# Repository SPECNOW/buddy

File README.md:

buddy
=====

# SPEC Robot
Clark Was able to clone this repository located at 
git@github.com:SPECNOW/buddy.git

## ADC Module
* Uses ADC and nHET modules
* Using 6 channels on ADC with nHET1_8 as the Triggger
* nHET PWM set for nHET1_8 @ 50% Duty Cycle @ 1 kHz
* Last 10 samples are reported by print ADC info

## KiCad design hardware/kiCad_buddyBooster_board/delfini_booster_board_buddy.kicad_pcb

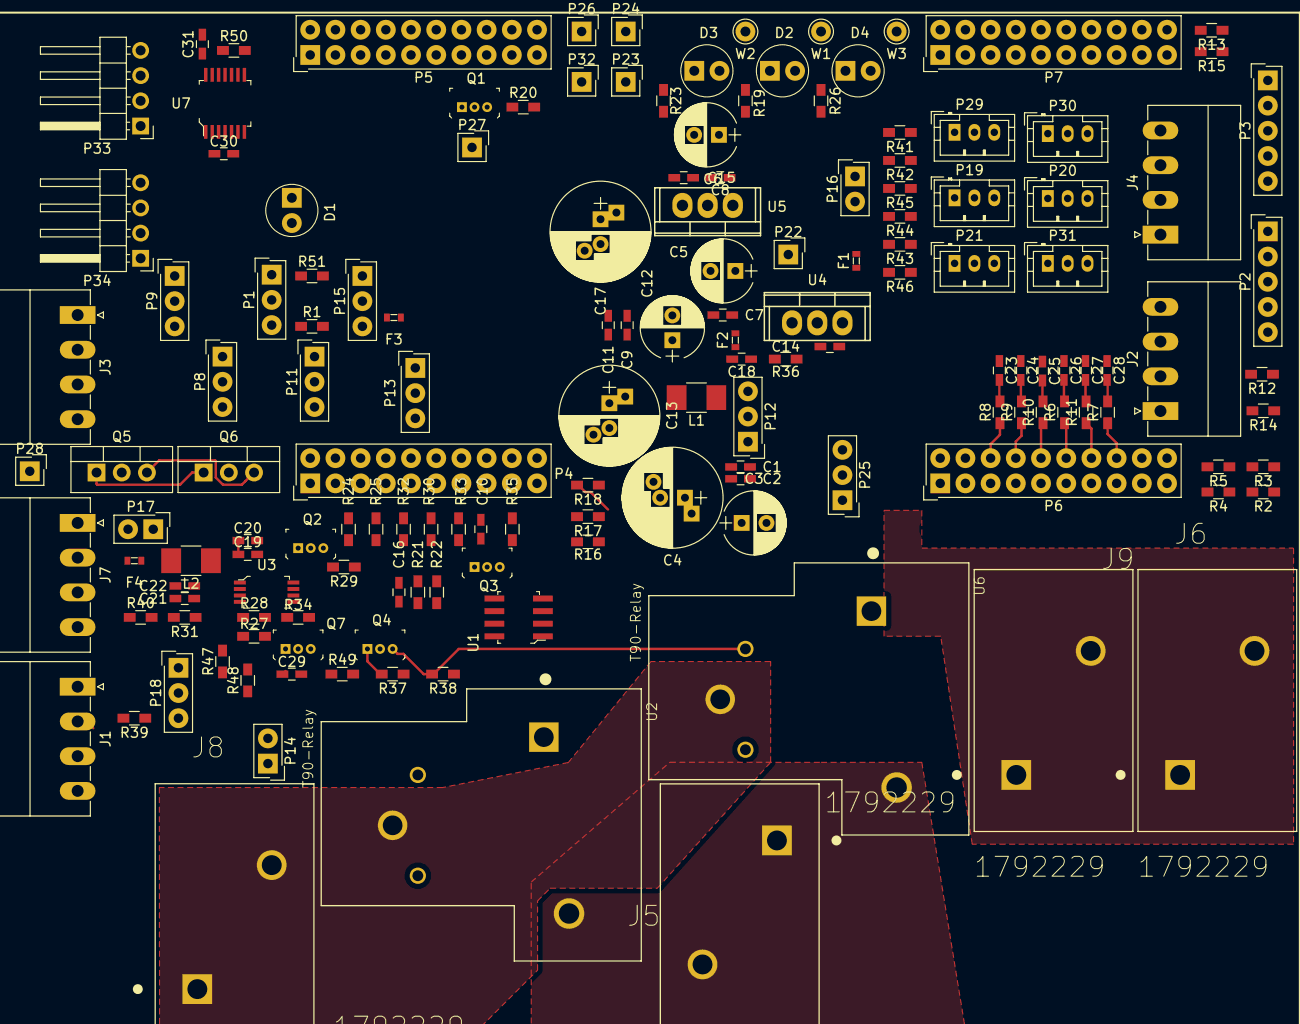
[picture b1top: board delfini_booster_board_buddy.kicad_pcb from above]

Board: 2 copper layers, 151 parts (0 on the bottom side), 88 nets.

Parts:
C1, C2, C7, C8, C9, C10, C11, C14, C15, C16, C19, C21, C23, C24, C25, C26, C27, C28, C29: C_Small; C_0603_HandSoldering
C3, C12: CP_Small; CP_Radial_D6.3mm_P2.50mm
C4, C13: CP_Small; CP_Radial_D10.0mm_P2.50mm_P5.00mm
C5, C6: CP1_Small; CP_Radial_D6.3mm_P2.50mm
C17: CP1_Small; CP_Radial_D10.0mm_P2.50mm_P5.00mm
C18, C20, C22: CP_Small; C_0603_HandSoldering
C30, C31: 0.1u; C_0603_HandSoldering
D1, D2, D3, D4: LED; LED_3mm_Radial
F1, F2, F3, F4: Fuse_Small; 0603
J1, J2, J3, J4, J7: Screw_Terminal_1x04; PhoenixContact_MC-G_04x3.50mm_Angled
J5, J6, J8, J9: 1792229; PHOENIX_1792229
L1, L2: Ferrite_Bead_Small; R_1210_HandSoldering
P1, P8, P9, P11, P12, P13, P15, P18, P25: CONN_01X03; SL-103-X-XX_1x03
P2, P3: CONN_01X05; SL-105-X-XX_1x05
P4, P5, P6, P7: CONN_02X10; SDL-120-X-XX_2x10
P14, P16, P17: CONN_01X02; SL-102-X-XX_1x02
P19, P20, P21, P29, P30, P31: CONN_01X03; JST_PH_B3B-PH-K_03x2.00mm_Straight
P22, P23, P24, P26, P27, P28, P32: CONN_01X01; SL-101-X-XX_1x01
P33, P34: CONN_01X04; Pin_Header_Angled_1x04_Pitch2.54mm
Q1, Q2, Q3, Q4, Q7: 2N7002; TO-92-3
Q5, Q6: IRF9540N; TO-220-3_Vertical
R1, R2, R3, R4, R5, R6, R7, R8, R9, R10, R11, R12, R13, R14, R15, R16, R17, R18, R19, R20, R21, R22, R23, R24, R25, R26, R27, R28, R29, R30, R31, R32, R33, R34, R35, R36, R37, R38, R39, R40, R41, R42, R43, R44, R45, R46, R47, R48, R49, R50, R51: R; R_0603_HandSoldering
U1: TMP275; SOIC-8_W3.9mm
U2, U6: T90-Relay; RELAY_1-1393209-2
U3: tps2112a; TSSOP-8_W4.4mm
U4: LM7812; TO-220
U5: R-783.3-1.0; TO-220
U7: TXB0104; TSSOP-14_W4.4mm
W1, W2, W3: TEST_1P; Pin_d1.0mm_L10.0mm

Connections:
+3V3: C16.2, C30.1, D3.2, F3.1, P26.1, R1.2, R2.1, R3.1, R16.1, R17.1, R18.1, R20.2, R21.1, R25.2, R31.2, R32.2, R35.2, R40.2, R47.2, R51.2, U1.8, U7.1, W2.1
+5V: C31.1, D2.2, P13.1, P17.1, P19.1, P20.1, P21.1, P24.1, P29.1, P30.1, P31.1, P33.1, P34.1, R12.2, R13.2, R14.2, R15.2, R50.1, U2.1, U7.14, W1.1
+12V: D4.2, J2.4, J4.4, P16.1, P23.1, W3.1
/5V_DEV_BRD: P8.2, R28.1, U3.6
/ADC0_IN_C2000: C23.2, R8.2, R41.2
/ADC0_OUTPUT: P29.2, R41.1
/ADC1_IN_C2000: C24.2, R9.2, R42.2
/ADC1_OUTPUT: P30.2, R42.1
/ADC2_IN_C2000: C25.2, R10.2, R43.2
/ADC2_OUTPUT: P31.2, R43.1
/ADC3_IN_C2000: C26.2, R6.2, R44.2
/ADC3_OUTPUT: P19.2, R44.1
/ADC4_IN_C2000: C27.2, R11.2, R45.2
/ADC4_OUTPUT: P20.2, R45.1
/ADC5_IN_C2000: C28.2, R7.2, R46.2
/ADC5_OUTPUT: P21.2, R46.1
/BAT_PWR_IN: C1.1, C2.1, C3.1, C4.1, J5.1, J5.2, P12.1, Q5.3, Q6.3, R49.2, U2.5, U6.5
/BAT_PWR_OUT: J8.1, J8.2, U2.3, U6.3
/BAT_PWR_OUT_DELFINO_EN: P5.1, R24.1
/BAT_PWR_OUT_EN: P11.1, Q2.1, Q4.1, R24.2, R25.1, R29.2, R37.2
/BRD_ID0: P6.17, R2.2, R4.1
/BRD_ID1: P6.19, R3.2, R5.1
/E_BRAKE_EN: P9.1, Q1.1, Q3.3, R35.1
/E_BRAKE_IN: J1.2, P18.3, R30.2
/LAUNCHPAD_5V: P4.2, P6.2, P8.1
/LaunchPad_3V3: P4.1, P6.1, P15.3
/MOTOR_BRAKE_EN: P9.2, R47.1, R48.2
/MOTOR_BRAKE_EN_N: Q5.1, Q6.1, Q7.3, R49.1
/RELAY_COIL: Q2.3, R38.1, U2.2
/SABERTOOTH_5V: J7.3, R27.2, U3.8
/SCL_4.7K: P4.19, R17.2, U1.2
/SDA_4.7K: P4.17, R16.2, U1.1
/TEST_EN_N: P1.3, P4.5, R1.1
/TMP275_ALERT_OD: P4.15, R18.2, U1.3
/TO_ENCODER_L_A: J2.3, P2.1
/TO_ENCODER_L_B: J2.2, P2.2
/TO_ENCODER_R_A: J4.3, P3.1
/TO_ENCODER_R_B: J4.2, P3.2
/TPS_STAT: R31.1, U3.1
/UART_SABER_TX: J7.1, P6.13
/ULTRA0_PULSE_BACK: P33.3, U7.12
/ULTRA0_PULSE_BACK_BUFFD: P5.9, U7.3
/ULTRA0_TRIG_OUT: P33.2, U7.13
/ULTRA0_TRIG_OUT_BUFFD: P5.5, U7.2
/ULTRA1_PULSE_BACK: P34.3, U7.10
/ULTRA1_PULSE_BACK_BUFFD: P5.11, U7.5
/ULTRA1_TRIG_OUT: P34.2, U7.11
/ULTRA1_TRIG_OUT_BUFFD: P5.7, U7.4
GND: C1.2, C2.2, C3.2, C4.2, C5.2, C6.2, C7.2, C8.2, C9.2, C10.1, C11.2, C12.2, C13.2, C14.2, C15.2, C16.1, C17.2, C19.2, C20.2, C21.2, C22.2, C23.1, C24.1, C25.1, C26.1, C27.1, C28.1, C29.2, C30.2, C31.2, D1.1, J2.1, J3.2, J3.4, J4.1, J7.4, P1.2, P2.5, P3.5, P4.4, P5.2, P6.4, P7.2, P14.2, P19.3, P20.3, P21.3, P25.2, P27.1, P28.1, P29.3, P30.3, P31.3, P32.1, P33.4, P34.4, Q1.2, Q2.2, Q3.2, Q4.2, Q7.2, R4.2, R5.2, R19.2, R22.1, R23.2, R26.2, R29.1, R33.1, R34.2, R36.1, R37.1, R39.2, U1.4, U1.5, U1.6, U3.5, U4.2, U5.2, U7.7
unnamed: C10.2, Q3.1, R30.1, R32.1, R33.2
unnamed: C9.1, C11.1, C12.1, C13.1, C18.1, F2.1, L1.2
unnamed: C14.1, F1.1, U4.3
unnamed: C15.1, C17.1, P15.1, U5.3
unnamed: C18.2, R36.2
unnamed: C19.1, C20.1, L2.1, U3.7
unnamed: C21.1, C22.1, F4.1, L2.2
unnamed: C29.1, Q7.1, R48.1
unnamed: D1.2, P1.1, R51.1
unnamed: D2.1, R19.1
unnamed: D3.1, R23.1
unnamed: D4.1, R26.1
unnamed: F1.2, P16.2
unnamed: F3.2, P15.2
unnamed: F4.2, P17.2
unnamed: J1.1, P18.2, R39.1, R40.1
unnamed: J3.1, Q6.2
unnamed: J3.3, Q5.2
unnamed: J6.1, J6.2, J9.1, J9.2, P25.1
unnamed: L1.1, P12.2
unnamed: P2.3, R12.1
unnamed: P2.4, R14.1
unnamed: P3.3, R13.1
unnamed: P3.4, R15.1
unnamed: P6.6, R8.1
unnamed: P6.8, R9.1
unnamed: P6.10, R10.1
unnamed: P6.12, R6.1
unnamed: P6.14, R11.1
unnamed: P6.16, R7.1
unnamed: P11.2, Q1.3, R20.1
unnamed: P13.2, U6.1
unnamed: P14.1, U3.2
unnamed: Q4.3, R38.2, U6.2
unnamed: R21.2, R22.2, U1.7
unnamed: R27.1, R28.2, U3.3
unnamed: R34.1, U3.4
unnamed: R50.2, U7.8
VAA: C5.1, C6.1, C7.1, C8.1, F2.2, P22.1, U4.1, U5.1

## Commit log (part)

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2013-12-13 create folder structure
2013-12-13 Clark modified README.md for his first git clone and git add, git commit and git push eventually. try using git commit -m "here is your one liner comment"
2014-05-30 tracking the green plate successful.
2014-06-06 swich from searching the whole image to scanning the submat but it crashes when it moves off screen
2014-06-09 Added Additional changes
2014-06-20 Changed the Image Data from a Depth Cloud to a Point Cloud for the Depth Converter. Added PointCloud Dependencies to project.
2014-06-26 Update DepthConverter.cpp
    We forgot to multiply the column index by 4.
2014-07-31 Ian finally does git. Also, this is a test
2014-08-04 Ian prepares for work on github
    ARM stuff works so testing the wireless MSP430 and writing dead reckoning code is coming
2014-09-11 Added Sensor Classes for IR and Sonar
    + Added GP2Y0A21YK (Sharp IR) Sensor Library
    + Created wrapper class for IR Sensor based off of common base Sensor
    Class
    + Added Sonar Sensor class based off of common base Sensor Class
2014-09-11 Motor turn with hardware serial1 on tx1
    We use the void setup to set up. use void loop for the main code.
    currently we have it sending 65 which is stop.
2014-09-11 interupt code change
    changed the interupt pin. it was 2 and 3, but instead use 0 and 1, as
    it is INTERUPT 0 and INTERUPT 1, not ... PIN3 PIN2.
    Have not tested with our set up. but i did simple test to turn some led
    on off and found the error
2014-09-11 Interrupts works- cleaned up testing code
    - Cleaned up some testing print outs
    - rearranged some function calls
2014-09-11 Revert "Update sketch_aug21a.ino"
    This reverts commit 9fc85e1593c4273154ef5ad6b182527779132d55.
2014-09-11 back update
    merged some changed.
2014-09-11 testing with encoder (fake)
    testing the QEM and the dir of encoder
2014-09-15 Fixed Sensor Class
    * Fixed Sonar and IR and verified that they are working correctly
    + Added Example Arduino Code for Sensor classes
2014-09-18 accident. ill revert
2014-09-18 Revert "accident. ill revert"
    This reverts commit 0923a94fb17245c32524b4a91cd5953422873def.
2014-10-02 Serial Test for MSP430G2553
    Tried Getting UART to work for MSP430, works by criss-crossing the RX
    and TX jumpers for Emultor board
2014-10-09 + Intial attemp at getting Buddy's Motor Controller to work on MSP430 MCU instead of Arduino. + Created Serial and MotorStateMachine Structs
2014-10-13 Fixed up previous code
    Code compiles correctly now, but doesn't work correctly. Further
    investigation needed.
2014-12-04 + Initial Commit of Hercules Buddy Motor Encoder Code
2015-09-10 Past 8 Months of work
    + ADC "working"
    + HET/Ultrasonic "working". Added Sonar Sensor Data Structures.
    + DAC working
    + Added Debugging/Info Message wrapper function (print_info, etc.)
    + Added Defines files for global variables
    + Fixed up Muxes/Interrupts/etc. in HalCoGen
2015-10-01 Moved our main project folder from Buddy_MotorEncoder_R4 to Buddy_Firmware_Hercules
2015-10-08 * Fixed Issue with BuddyFirmware_HalCoGen.hcg not working correctly (from previous commit) + Added rtiCounter for doing sonar PWM instead of HET (HET will still do the capture return from the sonar s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
2015-10-15 added ir_adc.h and .c created prototypes
2015-10-21 Sonar Sort of Works
    * nHET Capture returns Ultrasonic Pulse width correctly and calculates
    the distance correctly, but the Timeout implementation does not work
2016-01-21 Changed the method to do the Sonar Echo Capture to use RTI clock
    * Changed Sonar Echo Capture method to sample the RTI clock at the
    rising and falling edge of the Echo Signal and do math to figure out the
    signal width in milliseconds and then convert it to centimeters
    * RTI Trigger seems to have a problem with sonar 2, sonar 1 works fine
    both by itself and with sonar 2 enabled. May be due to interrupts for
    triggers for sonar 1 and sonar 2 happening at the same time?
2016-02-04 Added some comments for the Sonar/UltraSonic Stuff
    + Added some comments for the Sonar/UltraSonic Stuff
2016-03-31 Updated GitIgnore to Ignore C\C++, Python, Eclipse General Ignorable files
2016-03-31 removed laptop-software/motor-control-drivers/senor-to-laser/sensor-to-laser-base.py~
2016-04-07 -renamed senor-to-laser to sensor-to-laser
2016-04-14 Renamed the file so it would have _ instead of - in the name
2016-05-05 - created workspace in buddy/laptop-software - ros packages are in buddy/laptop-software/src/
2016-05-05 -moved some files into src
2016-05-05 Moving Serial Node to appropriate Folder
2016-06-02 * Updated Serial Node so that data is correctly extracted from serial data messages
2016-06-02 -added msg folder, didnt know it didnt work
2016-06-16 Made changes to CMake for Python
2016-07-14 Moved serial_node.py to scripts/ and made some minor fixes
2016-07-29 changed addCurrentToRosPackagePath and added python path, but make sure to catkin_make first
2016-07-29 Fixed: motor_control_drivers scripts serial_node.py
2016-08-04 Changed: Moved sensor_to_laser_base.py to scripts folder
2016-08-04 Startrted Ultrasonic"
2016-08-25 small updates to the ultrasonic and infrared nodes (not working)
2016-09-15 Redesign: sensor_to_laser_base to have base class for each sensor as a node which will subscribe to buddy msg and publish laser scan
2016-10-06 * Fixed up sensor_to_laser_base.py * Added sensor_to_laser to python Path * Changed BuddySerial.msg to make it eaier to use with sensor_to_laser_base
2016-10-13 * fixed toUpper() to upper()
2016-10-31 * Added Simulator * Added YAML files for Navigation Stack
2016-11-03 * Added Rviz Configuration
2016-12-15 * works wtih fake data from Hercules (should work with real data too for sesnors)
2017-01-05 * Removed extra Hal Co Gen files * Changed ADC Trigger (HET1_8) to be configured through Hal Co Gen instead of manually
2017-01-12 * Added comments to README.md
2017-02-02 Kind of cleaned up sonar
    * moved sonar functions and structures around a lot, kind of works
    (crashes when object too close)
2017-04-06 * fixed up serial with encoders (changed from float32 to uint32)
2017-04-12 * Created base file for motor control drivers
2017-04-19 Fixed Serial Packet structure
    * Fixed issues with sending encoder data (raw position count)
2017-05-10 * Stuff got fixed by updating ros * Changed rostopic queue sizes
2017-05-24 * made code structure for future work
2017-06-14 * Stuff works now (was wired incorrectly before) * Added a test script to check to ensure that positions only increase or decrease (direction changes are printed)
2017-09-06 * Added blank delfino driverlib project for buddy firmware
2017-09-28 * Added Project files
2017-10-19 updated todo.txt
2017-11-08 Enabled Serial Loopback: * Created Serial Initialization function * Made main function act as serial loopback for rxed serial data * works with arduino test code!! :D
2017-11-15 Made SCI use interrupts: * Untested, probably doesnt work
2017-11-22 Nov 14 test code
2017-11-22 PWMtestcode.ino -> created new file to do PWM. in the process of creating an array to accept multiple characters for PWM.
    171114Serialtest.ino -> added lines to break out of while loop if we don't receive anything from Delfino after 2 seconds. Confirm serial1 buffer is used correctly. It looks like we are able to receiv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
2017-11-29 Fixed Serial and added tests: * Fixed serial bug (clearing interrupt flag between initalizing modules) * Added pytest for serial loopback
2017-11-29 Fixed test name: * Changed test name to be more accurate * Added TX test (currently failing)
2017-12-13 -added 12v ldo -to do list added
2017-12-13 - spec out 2 relays T90S1D12-12 - need protection circuit for the regulators - need protection for relay switching.
2018-01-10 * Made Pytest compile and upload Arduino code (Not working)
2018-01-17 Fixed Serial Tests: * Made new INO files with better names * Made Arduino Compuile and upload INO files for each test
2018-01-17 Made main test script work
2018-01-31 - added snubber - added to todo list
2018-01-31 - rearranged blocks and gave them labels
2018-01-31 Small fix: * Killed eclipsec.exe after all tests are done
2018-02-07 - added second mosfet for relay turn on. Motor_bat
2018-02-07 Starting UltraSonic Test: * Started Ultrasonic Arduino test Code
2018-03-14 - Start to assign pin headers
2018-04-11 - Fixed encoder, no buffer required.
2018-04-11 * Changed Baude Rate to 115200 * Fixed up tests accordingly * reorganized code a bit * Remove Hercules code to clean up a bit
2018-04-27 - updated to-do
2018-05-11 Fixed up Ultrasonic Test code a bit more: * Enabled both tiggers
2018-05-16 - mapped more pcb foot print - imported t90 footprint, should be saved into temp local lib
2018-06-13 -mapped more 0.1 inch headers -bought 6p 0.1' pitch 20 pieces, delivery end of aug
2018-06-13 -got 2p, heavy current snapeda lib/footprint
2018-06-13 -todo:footprint check -sch symbol check- pin check -sch review -draw boardoutline and parts outline, measured location
2018-09-19 Updated to Kicad5, and added net to Launchpad headers
2019-01-16 - Mapped all components to footprint
2019-01-16 - Started placement, maybe not enough space
2019-01-25 - Placement of parts - Need relay protection for mosfet. and freewheel diode for load.
2019-01-30 - Placement grouped - added I2C - moved a few pins around. need FW sync with hw - connected UART to Sabertooth
2019-02-06 Modified tests: * modified test to not send pulses in interrupt * optimized code for more regular pulses and stuff
2019-02-20 -PCB- updated relay top silk -PCB- drawn outline in Tsilk
2019-02-20 -pcb- started routing
2019-02-27 Added averaging function * added function to return average of last N samples
2019-02-27 Tweak timeout: * timeout is 0xFF (as is super long respone)
2020-08-09 lock pyattrs to older version
2020-08-09 * Update tests to python3 * Update to CCS 10.10 * Change default project location for home PC (from laptop)
2020-08-31 * Simplify speed caclulation logic
2020-09-02 * Added tests for sabbertooth * Small fixes
2020-09-02 * Update serial stuff * Found reason for failing test, nothing we can do
2020-09-09 * Move Motor Variables to BuddyPacket from tests
2020-09-12 * Sabertooth BaudeRate is 384000
2020-09-18 -updated led debug_en circuit
2020-12-07 * Initialize GPIOs
2020-12-14 * fixed windows stuff a bit
2020-12-15 * Added rviz to docker-compose
2020-12-19 * updated docker-compose
2020-12-20 * moved Dockerfile
2020-12-20 * forgot hidden workspace file
2020-12-21 * fixed robot type
2020-12-22 * Added some instructions
2020-12-24 * fixed serial stuff
2020-12-29 * Use windows machine as display for now
